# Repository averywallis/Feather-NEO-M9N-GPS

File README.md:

# Feather-NEO-M9N-GPS
 KiCad files for a NEO-M9N GPS Featherwing

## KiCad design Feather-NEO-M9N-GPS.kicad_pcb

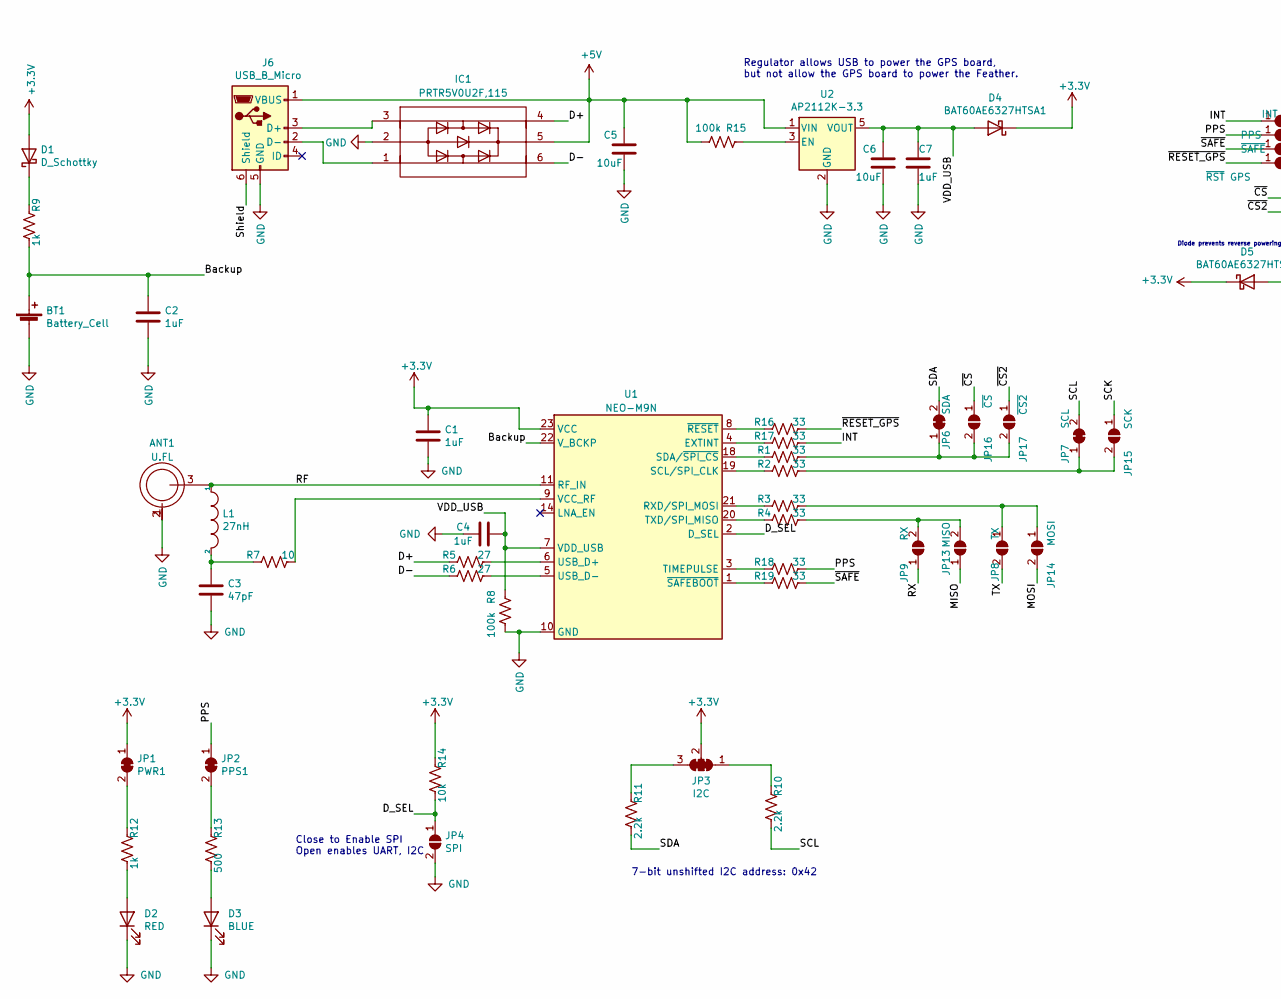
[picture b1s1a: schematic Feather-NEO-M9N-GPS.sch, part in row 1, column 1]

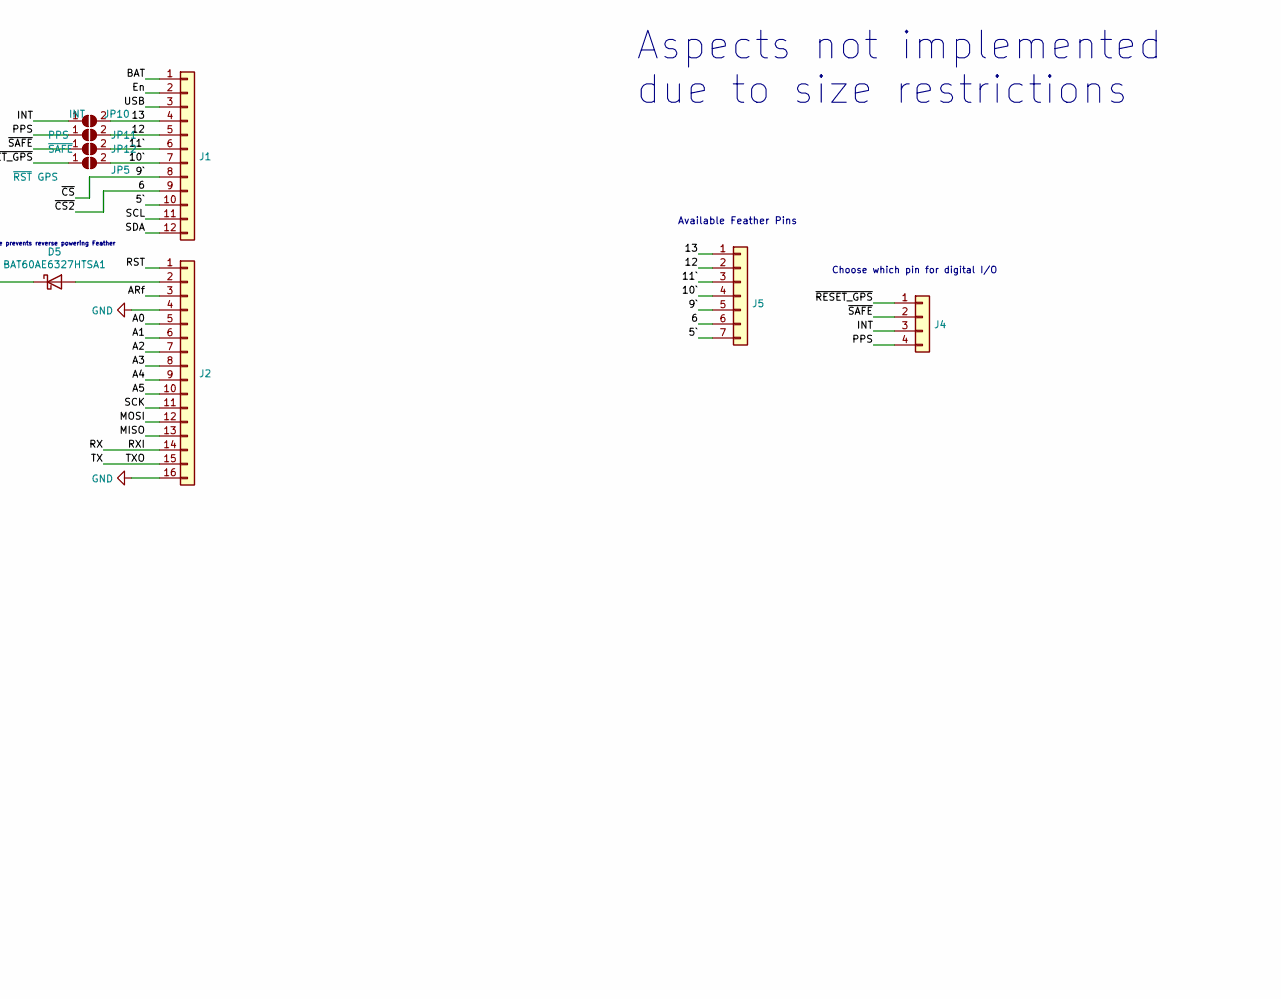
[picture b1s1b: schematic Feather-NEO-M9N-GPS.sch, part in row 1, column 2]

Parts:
ANT1: U.FL; UFLRSMT10; MPN U.FL-R-SMT(10)
BT1: Battery_Cell; BatteryHolder_Seiko_MS621F; MPN MS621FE-FL11E
C1, C2, C4, C7: 1uF; C_0603_1608Metric; MPN CL10A105KA8NNNC
C3: 47pF; C_0603_1608Metric; MPN GRM1885C1H470FA01J
C5, C6: 10uF; C_0603_1608Metric; MPN GRM188R61C106KAALD
D1: D_Schottky; D_SOD-323F; MPN PMEG4005EJF
D2: RED; LED_0603_1608Metric; MPN SML-D12V8WT86
D3: BLUE; LED_0603_1608Metric; MPN 598-8091-107F
D4, D5: BAT60AE6327HTSA1; SOD2513X110N; MPN BAT60AE6327HTSA1
IC1: PRTR5V0U2F,115; 74LVC1G27GM115; MPN PRTR5V0U2F,115
J1: PinHeader_1x12_P2.54mm_Vertical
J2: PinHeader_1x16_P2.54mm_Vertical
J4: PinHeader_1x04_P2.54mm_Vertical
J5: PinHeader_1x07_P2.54mm_Vertical
J6: USB_B_Micro; USB_Micro-B_Molex_47346-0001; MPN 47346-0001
JP1: PWR1; SolderJumper-2_P1.3mm_Bridged_RoundedPad1.0x1.5mm
JP2: PPS1; SolderJumper-2_P1.3mm_Bridged_RoundedPad1.0x1.5mm
JP3: I2C; SMT-JUMPER_3_2-NC_TRACE_SILK
JP4: SPI; SolderJumper-2_P1.3mm_Open_RoundedPad1.0x1.5mm
JP5: ~RST GPS; SolderJumper-2_P1.3mm_Open_RoundedPad1.0x1.5mm
JP6: SDA; SolderJumper-2_P1.3mm_Bridged_RoundedPad1.0x1.5mm
JP7: SCL; SolderJumper-2_P1.3mm_Bridged_RoundedPad1.0x1.5mm
JP8: TX; SolderJumper-2_P1.3mm_Open_RoundedPad1.0x1.5mm
JP9: RX; SolderJumper-2_P1.3mm_Open_RoundedPad1.0x1.5mm
JP10: INT; SolderJumper-2_P1.3mm_Open_RoundedPad1.0x1.5mm
JP11: PPS; SolderJumper-2_P1.3mm_Open_RoundedPad1.0x1.5mm
JP12: ~SAFE; SolderJumper-2_P1.3mm_Open_RoundedPad1.0x1.5mm
JP13: MISO; SolderJumper-2_P1.3mm_Open_RoundedPad1.0x1.5mm
JP14: MOSI; SolderJumper-2_P1.3mm_Open_RoundedPad1.0x1.5mm
JP15: SCK; SolderJumper-2_P1.3mm_Open_RoundedPad1.0x1.5mm
JP16: ~CS; SolderJumper-2_P1.3mm_Open_RoundedPad1.0x1.5mm
JP17: ~CS2; SolderJumper-2_P1.3mm_Open_RoundedPad1.0x1.5mm
L1: 27nH; L_0805_2012Metric; MPN CE201210-27NJ
R1, R2, R3, R4, R16, R17, R18, R19: 33; R_0402_1005Metric; MPN ESR03EZPJ330
R5, R6: 27; R_0603_1608Metric; MPN ERJ-PA3F27R0V
R7: 10; R_0603_1608Metric; MPN ESR03EZPF10R0
R8, R15: 100k; R_0603_1608Metric; MPN ESR03EZPF1003
R9, R12: 1k; R_0603_1608Metric; MPN ESR03EZPJ102
R10, R11: 2.2k; R_0603_1608Metric; MPN ESR03EZPJ222
R13: 500; R_0603_1608Metric; MPN ESR03EZPJ102
R14: 10k; R_0603_1608Metric; MPN ESR03EZPJ103
U1: NEO-M9N
U2: AP2112K-3.3; SOT-23-5; MPN AP2112K-3.3TRG1

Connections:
+3V3: C1.2, D1.2 (A), D4.1 (K), D5.1 (K), JP1.1 (A), JP3.2 (C), R14.2, U1.23 (VCC)
+5V: C5.2, IC1.5, J6.1 (VBUS), R15.1, U2.1 (VIN)
/5`: J1.10, J5.7
/6: J1.9, J5.6, JP17.1 (A)
/9`: J1.8, J5.5, JP16.1 (A)
/10`: J1.7, J5.4, JP5.2 (B)
/11`: J1.6, J5.3, JP12.2 (B)
/12: J1.5, J5.2, JP11.2 (B)
/13: J1.4, J5.1, JP10.2 (B)
/A0: J2.5
/A1: J2.6
/A2: J2.7
/A3: J2.8
/A4: J2.9
/A5: J2.10
/ARf: J2.3
/BAT: J1.1
/Backup: BT1.1 (+), C2.2, R9.1, U1.22 (V_BCKP)
/D+: IC1.4, R5.2
/D-: IC1.6, R6.2
/D_SEL: JP4.1 (A), R14.1, U1.2 (D_SEL)
/En: J1.2
/INT: J4.3, JP10.1 (A), R17.1
/MISO: J2.13, JP13.1 (A)
/MOSI: J2.12, JP14.2 (B)
/PPS: J4.4, JP2.1 (A), JP11.1 (A), R18.1
/RF: ANT1.3, L1.1, U1.11 (RF_IN)
/RST: J2.1
/RX: J2.14, JP9.1 (A)
/SCK: J2.11, JP15.1 (A)
/SCL: J1.11, JP7.2 (B), R10.1
/SDA: J1.12, JP6.2 (B), R11.1
/Shield: J6.6 (Shield)
/TX: J2.15, JP8.2 (B)
/USB: J1.3
/VDD_USB: C4.2, C6.2, C7.2, D4.2 (A), R8.2, U1.7 (VDD_USB), U2.5 (VOUT)
/~RESET_GPS: J4.1, JP5.1 (A), R16.1
/~SAFE: J4.2, JP12.1 (A), R19.1
GND: ANT1.1, ANT1.2, BT1.2 (-), C1.1, C2.1, C3.1, C4.1, C5.1, C6.1, C7.1, D2.1 (K), D3.1 (K), IC1.2, J2.4, J2.16, J6.5 (GND), JP4.2 (B), R8.1, U1.10 (GND), U1.12 (GND), U1.13 (GND), U1.24 (GND), U2.2 (GND)
unnamed: C3.2, L1.2, R7.2
unnamed: D1.1 (K), R9.2
unnamed: D2.2 (A), R12.1
unnamed: D3.2 (A), R13.1
unnamed: D5.2 (A), J2.2
unnamed: IC1.1, J6.2 (D-)
unnamed: IC1.3, J6.3 (D+)
unnamed: JP1.2 (B), R12.2
unnamed: JP2.2 (B), R13.2
unnamed: JP3.1 (A), R10.2
unnamed: JP3.3 (B), R11.2
unnamed: JP9.2 (B), JP13.2 (B), R4.1
unnamed: JP8.1 (A), JP14.1 (A), R3.1
unnamed: JP7.1 (A), JP15.2 (B), R2.1
unnamed: JP6.1 (A), JP16.2 (B), JP17.2 (B), R1.1
unnamed: R1.2, U1.18 (SDA/~SPI_CS)
unnamed: R2.2, U1.19 (SCL/SPI_CLK)
unnamed: R3.2, U1.21 (RXD/SPI_MOSI)
unnamed: R4.2, U1.20 (TXD/SPI_MISO)
unnamed: R5.1, U1.6 (USB_D+)
unnamed: R6.1, U1.5 (USB_D-)
unnamed: R7.1, U1.9 (VCC_RF)
unnamed: R15.2, U2.3 (EN)
unnamed: R16.2, U1.8 (~RESET)
unnamed: R17.2, U1.4 (EXTINT)
unnamed: R18.2, U1.3 (TIMEPULSE)
unnamed: R19.2, U1.1 (~SAFEBOOT)

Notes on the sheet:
Close to Enable SPI Open enables UART, I2C
Available Feather Pins
Regulator allows USB to power the GPS board, but not allow the GPS board to power the Feather.
Diode prevents reverse powering Feather
7-bit unshifted I2C address: 0x42
Aspects not implemented due to size restrictions
Choose which pin for digital I/O

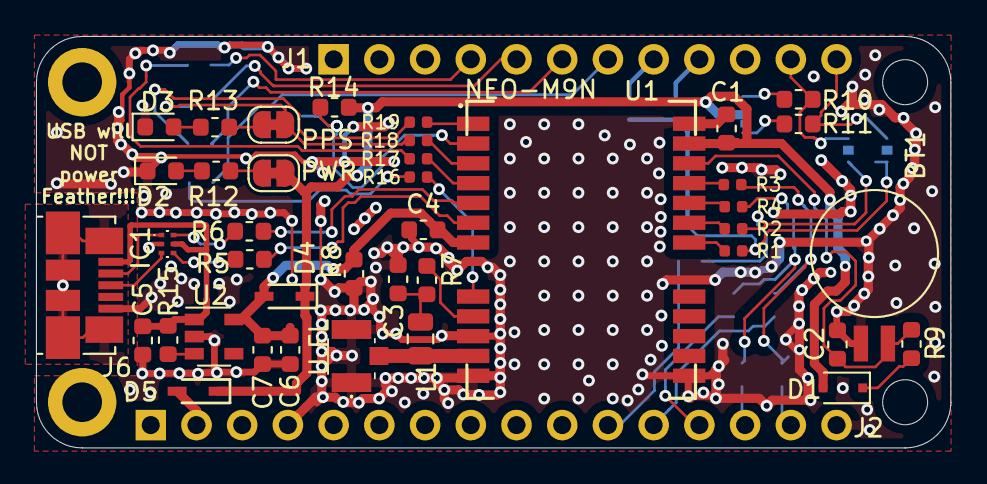
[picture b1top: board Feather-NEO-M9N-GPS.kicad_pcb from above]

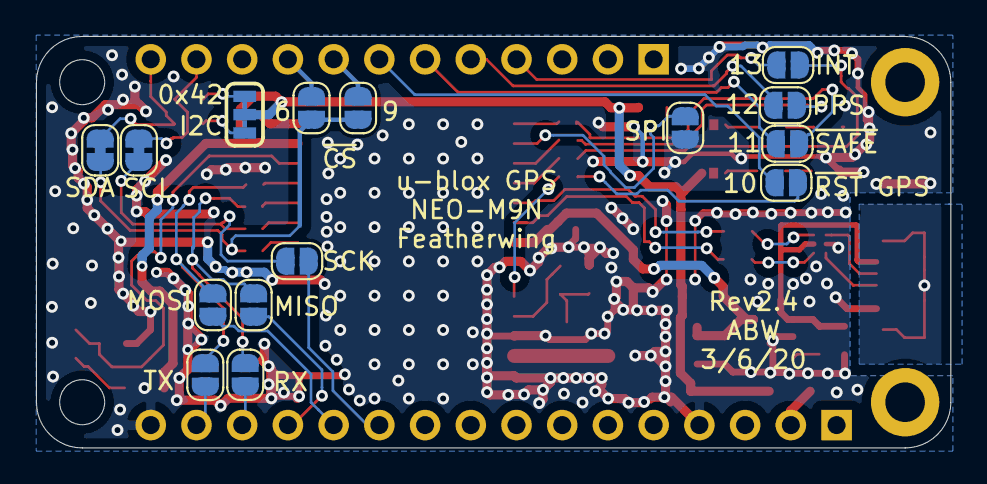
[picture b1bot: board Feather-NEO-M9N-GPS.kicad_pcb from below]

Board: 2 copper layers, 50.8 x 22.9 mm, 57 parts (15 on the bottom side), 53 nets.

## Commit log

2020-01-06 Rev2!
    Rev2 includes proper USB implementation, some small trace fixes, and power regulation
2020-01-06 Added .GBR and images
2020-01-06 Added KiCad file Archive of Rev2
2020-01-15 Added a pdf of the schematic for sharing
2020-01-24 Rev2.1 of NEO-M9N
2020-02-01 Rev 2.2 designed
    Lots of great feedback from the u-blox team. Hopefully this revision fixes a lot of the problems they pointed out
2020-02-26 Rev 2.3, u-blox approved!
    Rev 2.3 is finished! It has been approved by the design team at u-blox. Next step is to see if Adafruit would be interested in my continuing this design and possibly getting it onto their store if it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
2020-02-28 added photos, schematic, zip of files
2020-03-06 Added additional CS pin. Kept caps as is because of integration manual
2022-01-29 Create LICENSE
